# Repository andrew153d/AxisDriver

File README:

# Axis Driver #

# Json interface #

- To run the motor:
 ```
 {
  "type":"MOVEMENT",
  "mode": "POSITION",
  "steps": 1000,
  "speed": 100, 
  "stepmode": 64,
  "hold": 0
  }
```

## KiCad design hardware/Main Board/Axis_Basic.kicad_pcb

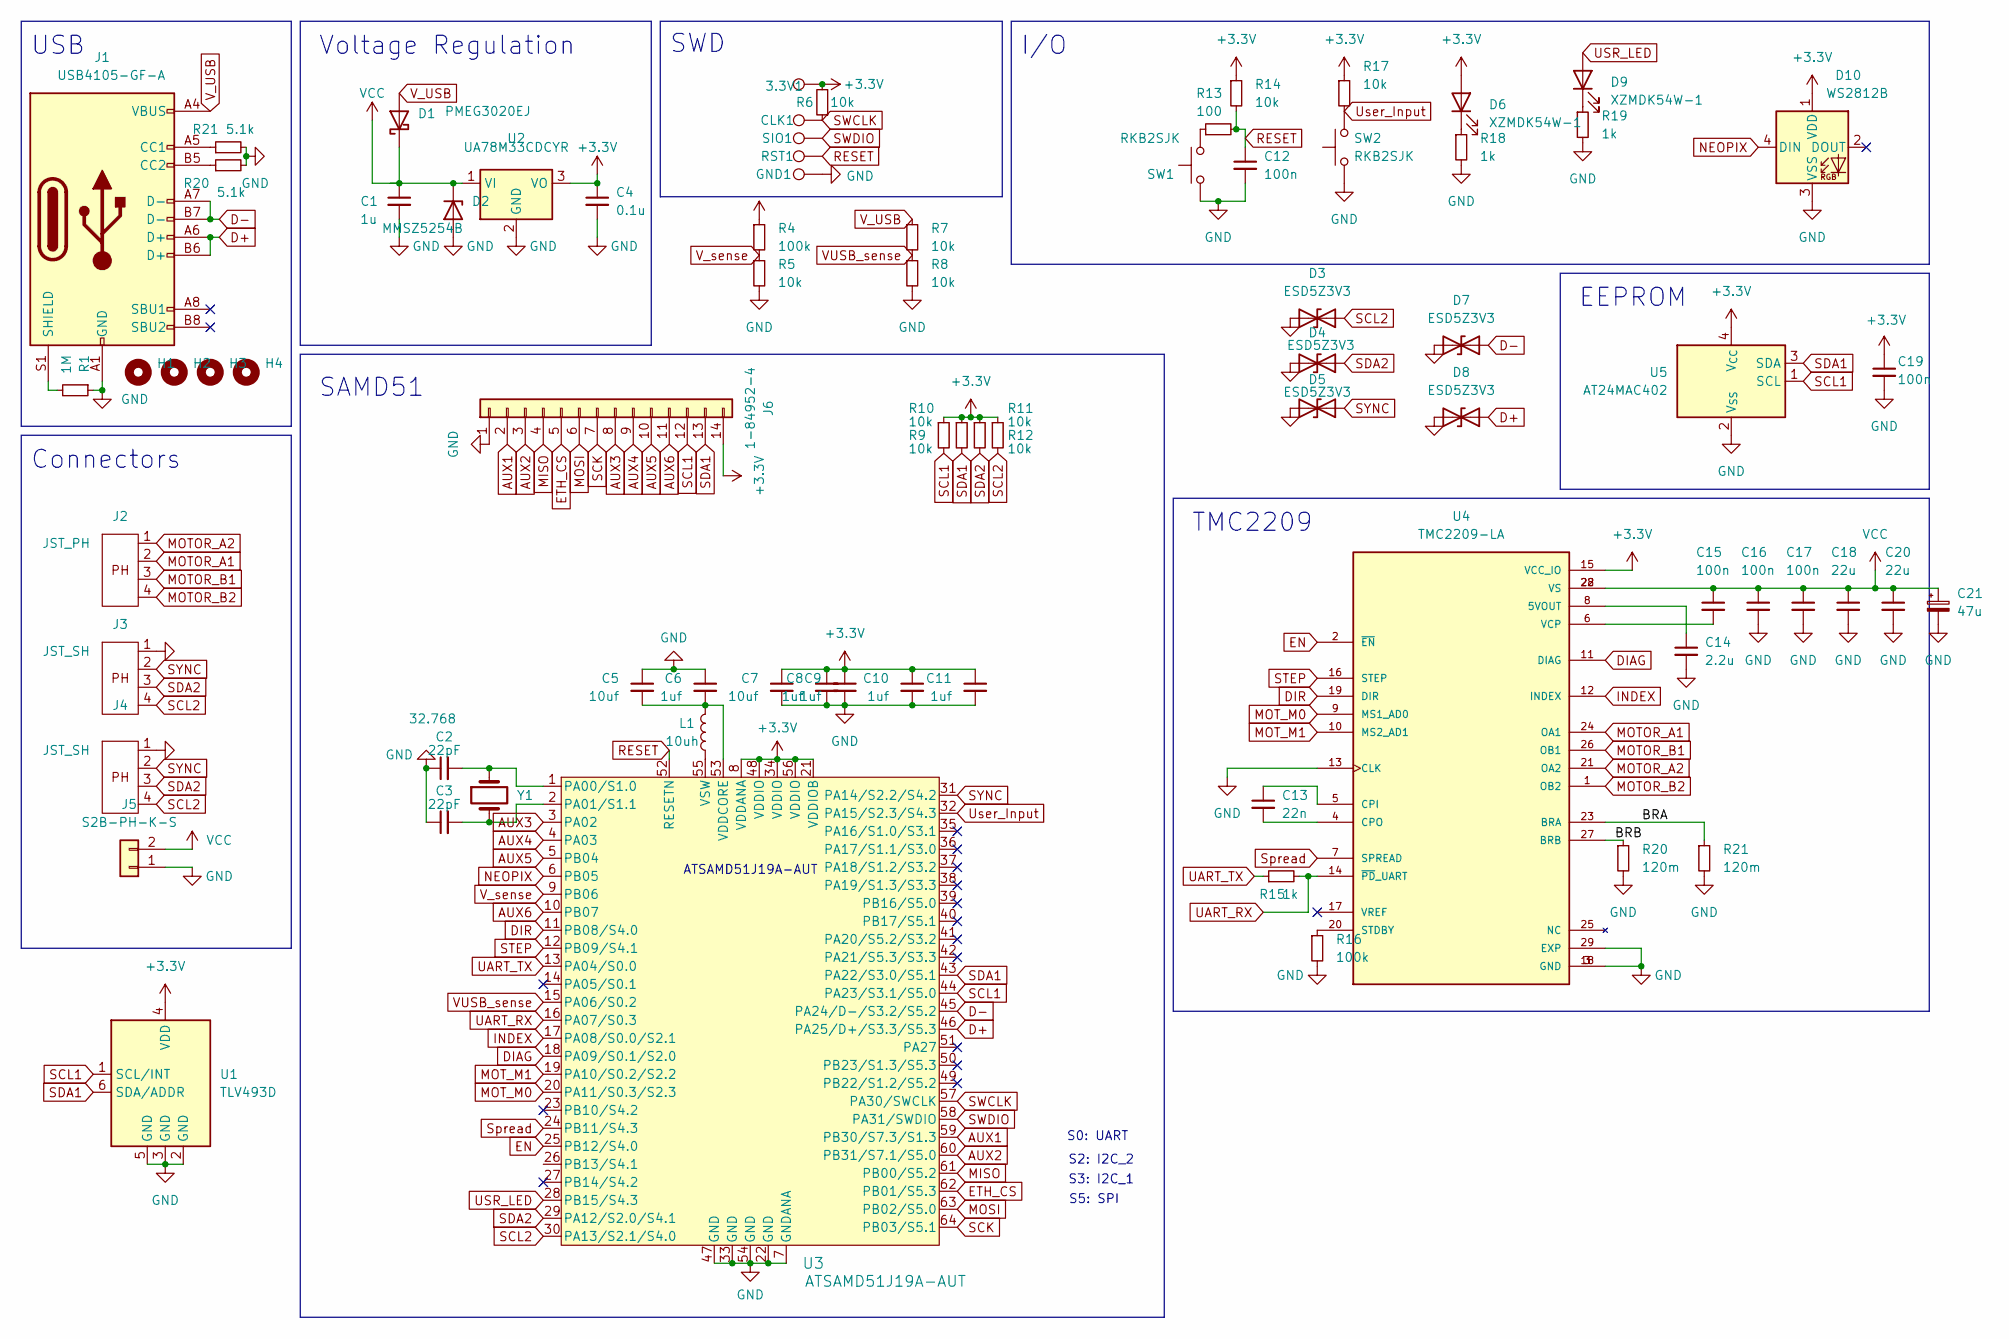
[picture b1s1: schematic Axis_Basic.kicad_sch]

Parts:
3.3V1: TestPoint; TestPoint_Pad_D2.0mm
C1: 1u; C_0402_1005Metric
C2, C3: 22pF; C_0402_1005Metric
C4: 0.1u; C_0402_1005Metric
C5, C7: 10uf; C_0805_2012Metric
C6, C8, C9, C10, C11: 1uf; C_0402_1005Metric
C12, C15, C16, C17, C19: 100n; C_0402_1005Metric
C13: 22n; C_0402_1005Metric
C14: 2.2u; C_0402_1005Metric
C18, C20: 22u; C_0805_2012Metric
C21: 47u; CP_Elec_6.3x5.4
CLK1: TestPoint; TestPoint_Pad_D2.0mm
D1: PMEG3020EJ; D_SOD-323F
D2: MMSZ5254B; D_SOD-123
D3, D4, D5, D7, D8: ESD5Z3V3; D_SOD-523
D6, D9: XZMDK54W-1; LED_0603_1608Metric
D10: WS2812B; LED_WS2812B_PLCC4_5.0x5.0mm_P3.2mm
GND1: TestPoint; TestPoint_Pad_D2.0mm
H1, H2, H3, H4: MountingHole; MountingHole_3.2mm_M3_ISO14580_Pad
J1: USB4105-GF-A; USB_C_Receptacle_GCT_USB4105-xx-A_16P_TopMnt_Horizontal
J2: JST_PH; JST_PH_S4B-PH-K_1x04_P2.00mm_Horizontal
J3, J4: JST_SH; JST_SH_SM04B-SRSS-TB_1x04-1MP_P1.00mm_Horizontal
J5: S2B-PH-K-S; JST_PH_S2B-PH-K_1x02_P2.00mm_Horizontal
J6: 1-84952-4; TE_1-84952-4_1x14-1MP_P1.0mm_Horizontal
L1: 10uh; L_0603_1608Metric
R1: 1M; R_0402_1005Metric
R4, R16: 100k; R_0402_1005Metric
R5, R6, R7, R8, R9, R10, R11, R12, R14, R17: 10k; R_0402_1005Metric
R13: 100; R_0402_1005Metric
R15, R18, R19: 1k; R_0402_1005Metric
R20, R21: 5.1k; R_0402_1005Metric
RST1: TestPoint; TestPoint_Pad_D2.0mm
SIO1: TestPoint; TestPoint_Pad_D2.0mm
SW1, SW2: RKB2SJK; button_RKB2SJK250SMTR LFS
U1: TLV493D; SOT-23-6
U2: UA78M33CDCYR; SOT-223-3_TabPin2
U3: ATSAMD51J19A-AUT; TQFP-64_10x10mm_P0.5mm
U4: TMC2209-LA; QFN-28-1EP_5x5mm_P0.5mm_EP3.35x3.35mm_ThermalVias; PARTREV 1.08
U5: AT24MAC402; SOT-23-5
Y1: 32.768; Crystal_SMD_3215-2Pin_3.2x1.5mm

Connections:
+3.3V: 3.3V1.1, C4.1, C7.1, C8.1, C9.1, C10.1, C11.1, C19.1, D6.2 (A), D10.1 (VDD), J6.14, R6.2, R9.1, R10.1, R11.1, R12.1, R14.1, R17.1, U1.4 (VDD), U2.3 (VO), U3.8 (VDDANA), U3.21 (VDDIOB), U3.34 (VDDIO), U3.48 (VDDIO), U3.56 (VDDIO), U4.15 (VCC_IO), U5.4 (V_{CC})
AUX1: J6.2, U3.59 (PB30/S7.3/S1.3)
AUX2: J6.3, U3.60 (PB31/S7.1/S5.0)
AUX3: J6.8, U3.3 (PA02)
AUX4: J6.9, U3.4 (PA03)
AUX5: J6.10, U3.5 (PB04)
AUX6: J6.11, U3.10 (PB07)
D+: D8.1 (A1), J1.A6 (D+), J1.B6 (D+), U3.46 (PA25/D+/S3.3/S5.3)
D-: D7.1 (A1), J1.A7 (D-), J1.B7 (D-), U3.45 (PA24/D-/S3.2/S5.2)
DIAG: U3.18 (PA09/S0.1/S2.0), U4.11 (DIAG)
DIR: U3.11 (PB08/S4.0), U4.19 (DIR)
EN: U3.25 (PB12/S4.0), U4.2 (~EN)
ETH_CS: J6.5, U3.62 (PB01/S5.3)
GND: C1.2, C2.1, C3.1, C4.2, C5.1, C6.1, C7.2, C8.2, C9.2, C10.2, C11.2, C12.2, C14.2, C16.2, C17.2, C18.2, C19.2, C20.2, C21.2, D2.2 (A), D3.2 (A2), D4.2 (A2), D5.2 (A2), D7.2 (A2), D8.2 (A2), D10.3 (VSS), GND1.1, J1.A1 (GND), J1.A12 (GND), J1.B1 (GND), J1.B12 (GND), J3.1, J4.1, J5.1, J6.1, R1.1, R5.2, R8.2, R16.2, R18.2, R19.2, R20.2, R21.2, SW1.1, SW2.1, U1.2 (GND), U1.3 (GND), U1.5 (GND), U2.2 (GND), U3.7 (GNDANA), U3.22 (GND), U3.33 (GND), U3.47 (GND), U3.54 (GND), U4.3 (GND), U4.13 (CLK), U4.18 (GND), U4.29 (EXP), U5.2 (V_{SS}); also elsewhere on the board
INDEX: U3.17 (PA08/S0.0/S2.1), U4.12 (INDEX)
MISO: J6.4, U3.61 (PB00/S5.2)
MOSI: J6.6, U3.63 (PB02/S5.0)
MOTOR_A1: J2.2, U4.24 (OA1)
MOTOR_A2: J2.1, U4.21 (OA2)
MOTOR_B1: J2.3, U4.26 (OB1)
MOTOR_B2: J2.4, U4.1 (OB2)
MOT_M0: U3.20 (PA11/S0.3/S2.3), U4.9 (MS1_AD0)
MOT_M1: U3.19 (PA10/S0.2/S2.2), U4.10 (MS2_AD1)
NEOPIX: D10.4 (DIN), U3.6 (PB05)
unnamed: D6.1 (K), R18.1
unnamed: D9.1 (K), R19.1
unnamed: J1.S1 (SHIELD), R1.2
unnamed: R13.1, SW1.2
unnamed: C2.2, U3.1 (PA00/S1.0), Y1.1
unnamed: C3.2, U3.2 (PA01/S1.1), Y1.2
unnamed: C5.2, C6.2, L1.2, U3.53 (VDDCORE)
unnamed: L1.1, U3.55 (VSW)
unnamed: C14.1, U4.8 (5VOUT)
unnamed: C13.1, U4.5 (CPI)
unnamed: C13.2, U4.4 (CPO)
unnamed: R16.1, U4.20 (STDBY)
unnamed: C15.2, U4.6 (VCP)
RESET: C12.1, R13.2, R14.2, RST1.1, U3.52 (RESETN)
SCK: J6.7, U3.64 (PB03/S5.1)
SCL1: J6.12, R9.2, U1.1 (SCL/INT), U3.44 (PA23/S3.1/S5.0), U5.1 (SCL)
SCL2: D3.1 (A1), J3.4, J4.4, R12.2, U3.30 (PA13/S2.1/S4.0)
SDA1: J6.13, R10.2, U1.6 (SDA/ADDR), U3.43 (PA22/S3.0/S5.1), U5.3 (SDA)
SDA2: D4.1 (A1), J3.3, J4.3, R11.2, U3.29 (PA12/S2.0/S4.1)
STEP: U3.12 (PB09/S4.1), U4.16 (STEP)
SWCLK: CLK1.1, R6.1, U3.57 (PA30/SWCLK)
SWDIO: SIO1.1, U3.58 (PA31/SWDIO)
SYNC: D5.1 (A1), J3.2, J4.2, U3.31 (PA14/S2.2/S4.2)
Spread: U3.24 (PB11/S4.3), U4.7 (SPREAD)
UART_RX: R15.2, U3.16 (PA07/S0.3), U4.14 (~PD_UART)
UART_TX: R15.1, U3.13 (PA04/S0.0)
USR_LED: D9.2 (A), U3.28 (PB15/S4.3)
User_Input: R17.2, SW2.2, U3.32 (PA15/S2.3/S4.3)
VCC: C1.1, C15.1, C16.1, C17.1, C18.1, C20.1, C21.1, D1.1 (K), D2.1 (K), J5.2, R4.1, U2.1 (VI), U4.22 (VS), U4.28 (VS)
VUSB_sense: R7.2, R8.1, U3.15 (PA06/S0.2)
V_USB: D1.2 (A), J1.A4 (VBUS), J1.A9 (VBUS), J1.B4 (VBUS), J1.B9 (VBUS), R7.1
V_sense: R4.2, R5.1, U3.9 (PB06)

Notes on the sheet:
S2: I2C_2
SAMD51
EEPROM
S3: I2C_1
Connectors
TMC2209
I/O
ATSAMD51J19A-AUT
Voltage Regulation
S0: UART
SWD
S5: SPI
USB

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
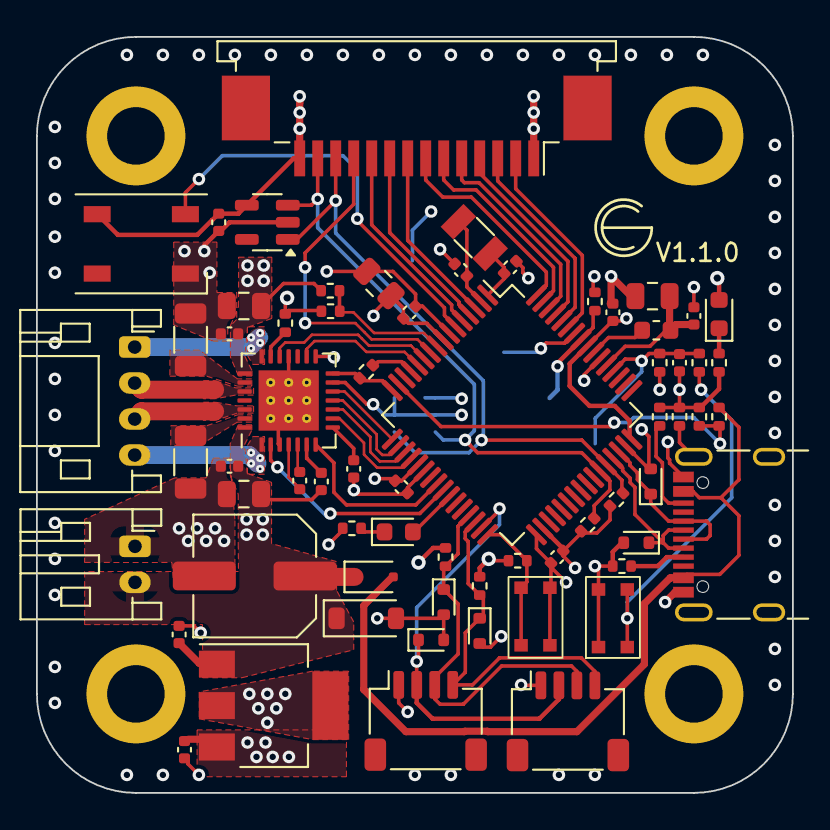
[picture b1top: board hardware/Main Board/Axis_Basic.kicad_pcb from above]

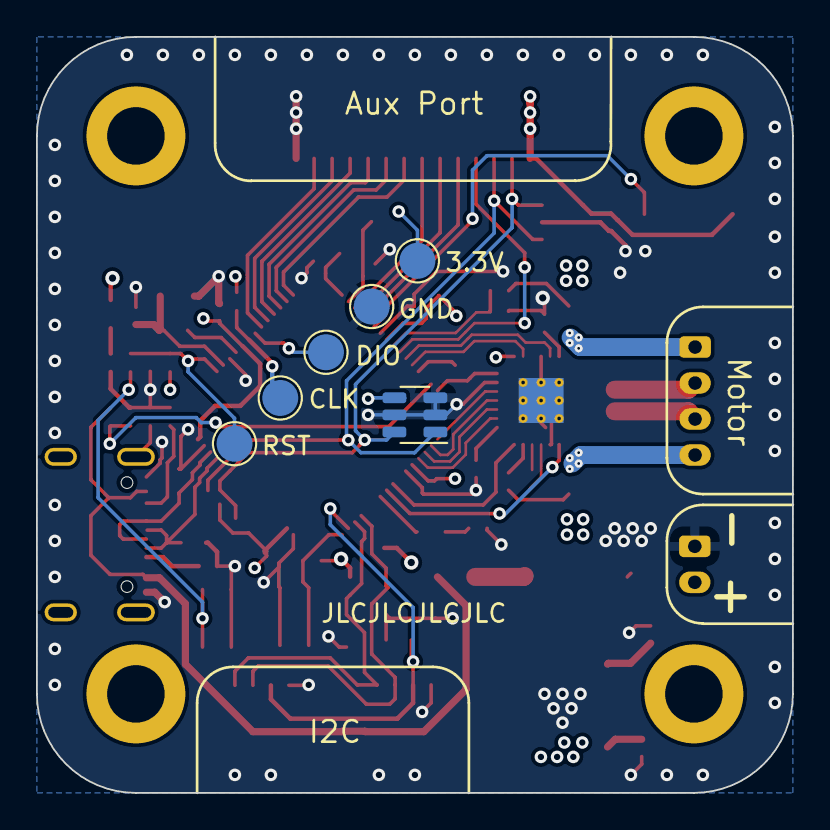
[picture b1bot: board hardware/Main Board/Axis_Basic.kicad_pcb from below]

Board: 4 copper layers, 42.0 x 42.0 mm, 76 parts (6 on the bottom side), 60 nets.

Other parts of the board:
R2, R3: 5.1k; R_0402_1005Metric

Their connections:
GND: R2.2, R3.2; also elsewhere on the board

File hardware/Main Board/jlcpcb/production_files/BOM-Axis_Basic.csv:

Comment,Designator,Footprint,LCSC
100n,"C12,C15",C_0402_1005Metric,C1525
10k,"R11,R12,R6,R9",R_0402_1005Metric,C25744
5.1k,"R2,R3",R_0402_1005Metric,C25905
1M,R1,R_0402_1005Metric,C26083
TMC2209-LA,U4,QFN-28-1EP_5x5mm_P0.5mm_EP3.35x3.35mm_ThermalVias,C465949
UA78M33CDCYR,U2,SOT-223-3_TabPin2,C49036
1uf,C6,C_0402_1005Metric,
22pF,C3,C_0402_1005Metric,
10k,R10,R_0402_1005Metric,
0.33u,C1,C_0402_1005Metric,
ESD5Z3V3,D4,D_SOD-523,
ATSAMD51J19A-AUT,U3,TQFP-64_10x10mm_P0.5mm,
JST_SH,J4,JST_SH_SM04B-SRSS-TB_1x04-1MP_P1.00mm_Horizontal,
ESD5Z3V3,D5,D_SOD-523,
10uf,C5,C_0805_2012Metric,
1-84952-4,J6,TE_1-84952-4_1x14-1MP_P1.0mm_Horizontal,
MountingHole,H1,MountingHole_3.2mm_M3_ISO14580_Pad,
1k,R15,R_0402_1005Metric,
100k,R4,R_0402_1005Metric,
1uf,C9,C_0402_1005Metric,
0.1u,C4,C_0402_1005Metric,
10k,R5,R_0402_1005Metric,
1uf,C8,C_0402_1005Metric,
JST_PH,J2,JST_PH_S4B-PH-K_1x04_P2.00mm_Horizontal,
ESD5Z3V3,D3,D_SOD-523,
32.768,Y1,Crystal_SMD_3215-2Pin_3.2x1.5mm,
10k,R8,R_0402_1005Metric,
MountingHole,H4,MountingHole_3.2mm_M3_ISO14580_Pad,
1uf,C11,C_0402_1005Metric,
100n,C17,C_0402_1005Metric,
XZMDK54W-1,D6,LED_0603_1608Metric,
100n,C16,C_0402_1005Metric,
ESD5Z3V3,D7,D_SOD-523,
1uf,C10,C_0402_1005Metric,
PMEG3020EJ,D1,D_SOD-323F,
RKB2SJK,SW1,button_RKB2SJK250SMTR LFS,
24AA02E-OT,U5,SOT-23-5,
22u,C18,C_0805_2012Metric,
2.2u,C14,C_0402_1005Metric,
RKB2SJK,SW2,button_RKB2SJK250SMTR LFS,
	MMSZ5254B,D2,D_SOD-123,
22pF,C2,C_0402_1005Metric,
10uf,C7,C_0805_2012Metric,
10k,R7,R_0402_1005Metric,
MountingHole,H3,MountingHole_3.2mm_M3_ISO14580_Pad,
22n,C13,C_0402_1005Metric,
300,R13,R_0402_1005Metric,
10k,R14,R_0402_1005Metric,
JST_SH,J3,JST_SH_SM04B-SRSS-TB_1x04-1MP_P1.00mm_Horizontal,
S2B-PH-K-S,J5,JST_PH_S2B-PH-K_1x02_P2.00mm_Horizontal,
MountingHole,H2,MountingHole_3.2mm_M3_ISO14580_Pad,
USB4105-GF-A,J1,USB_C_Receptacle_GCT_USB4105-xx-A_16P_TopMnt_Horizontal,
TLV493D,U1,SOT-23-6,
120m,R21,R_1206_3216Metric,
100k,R16,R_0402_1005Metric,
1k,R19,R_0402_1005Metric,
10uh,L1,L_0603_1608Metric,
47u,C21,CP_Elec_6.3x5.4,
XZMDK54W-1,D9,LED_0603_1608Metric,
22u,C20,C_0805_2012Metric,
100n,C19,C_0402_1005Metric,
1k,R18,R_0402_1005Metric,
10k,R17,R_0402_1005Metric,
WS2812B,D10,LED_WS2812B_PLCC4_5.0x5.0mm_P3.2mm,
120m,R20,R_1206_3216Metric,
ESD5Z3V3,D8,D_SOD-523,
TestPoint,GND1,TestPoint_Pad_D2.0mm,
TestPoint,CLK1,TestPoint_Pad_D2.0mm,
TestPoint,RST1,TestPoint_Pad_D2.0mm,
TestPoint,SIO1,TestPoint_Pad_D2.0mm,

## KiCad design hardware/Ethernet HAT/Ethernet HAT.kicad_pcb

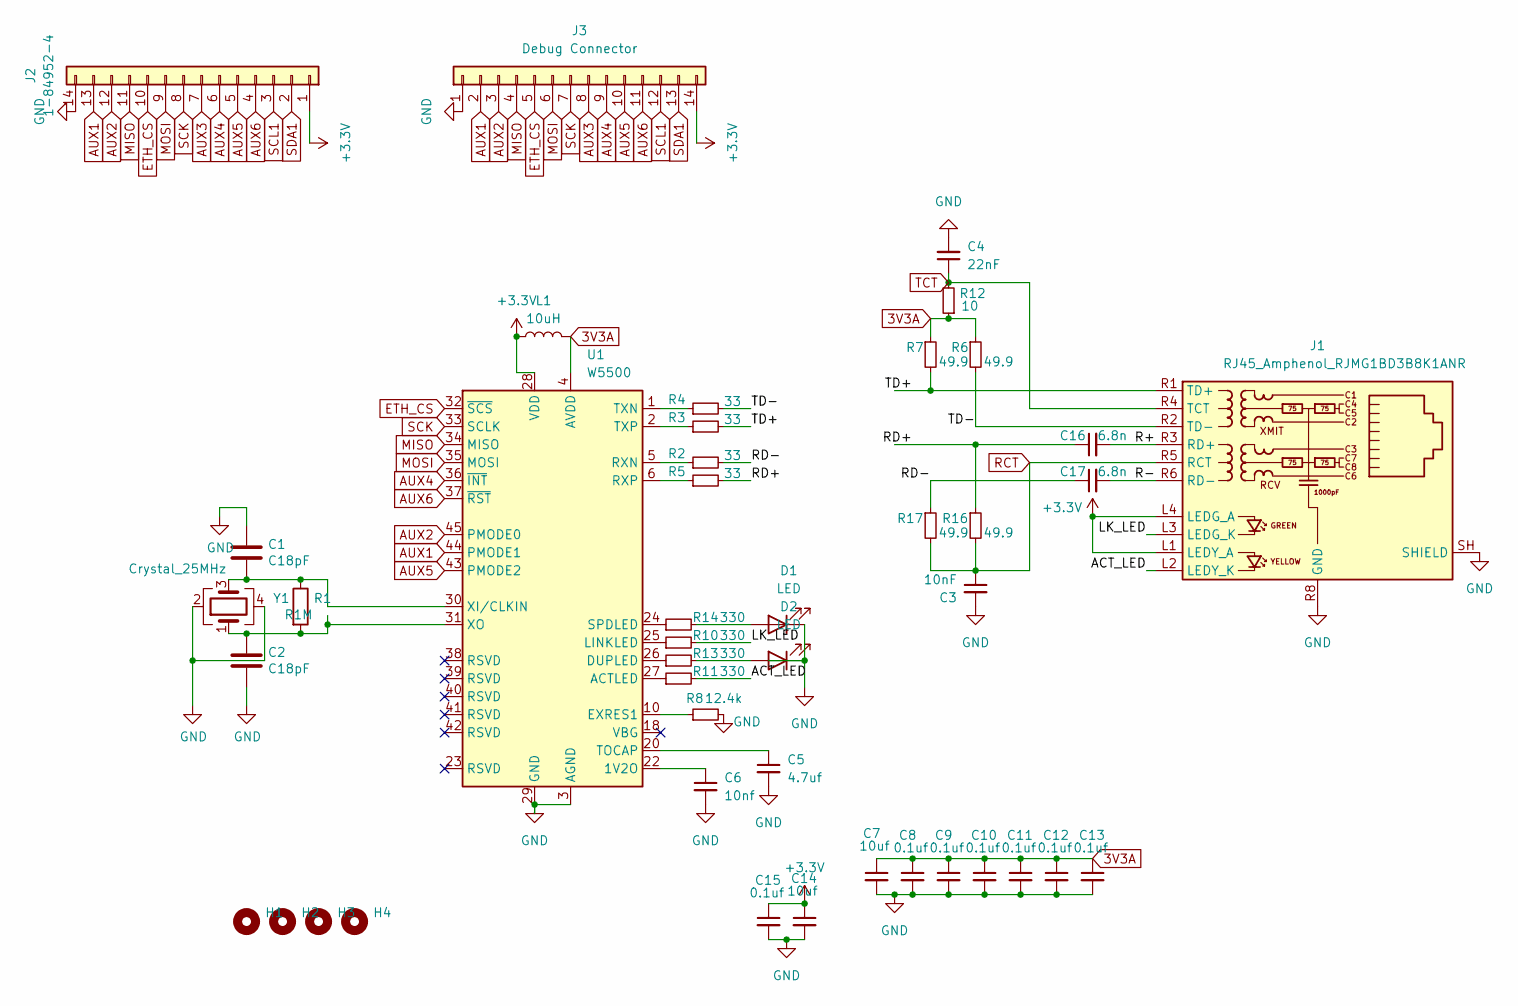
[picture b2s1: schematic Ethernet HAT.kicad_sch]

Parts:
C1, C2: C18pF; C_0402_1005Metric; LCSC C1549
C3: 10nF; C_0402_1005Metric
C4: 22nF; C_0402_1005Metric
C5: 4.7uf; C_0402_1005Metric
C6: 10nf; C_0402_1005Metric
C7, C14: 10uf; C_0805_2012Metric
C8, C9, C10, C11, C12, C13, C15: 0.1uf; C_0402_1005Metric
C16, C17: 6.8n; C_0402_1005Metric
D1, D2: LED; LED_0603_1608Metric
H1, H2, H3, H4: MountingHole; MountingHole_3.2mm_M3_ISO14580_Pad
J1: RJ45_Amphenol_RJMG1BD3B8K1ANR
J2: 1-84952-4; TE_1-84952-4_1x14-1MP_P1.0mm_Horizontal
J3: Debug Connector; Conn_01x14_Flat2.54
L1: 10uH; L_0603_1608Metric
R1: R1M; R_0402_1005Metric; LCSC C26083
R2, R3, R4, R5: 33; R_0402_1005Metric
R6, R7, R16, R17: 49.9; R_0402_1005Metric
R8: 12.4k; R_0603_1608Metric
R10, R11, R13, R14: 330; R_0402_1005Metric
R12: 10; R_0402_1005Metric
U1: W5500; LQFP-48_7x7mm_P0.5mm
Y1: Crystal_25MHz; Crystal_SMD_3225-4Pin_3.2x2.5mm; LCSC C9006

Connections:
3V3A: C7.1, C8.1, C9.1, C10.1, C11.1, C12.1, C13.1, L1.2, R6.1, R7.1, R12.1, U1.4 (AVDD), U1.8 (AVDD), U1.11 (AVDD), U1.15 (AVDD), U1.17 (AVDD), U1.21 (AVDD)
+3.3V: C14.1, C15.1, J1.L1 (LEDY_A), J1.L4 (LEDG_A), J2.1, J3.14, L1.1, U1.28 (VDD)
/ACT_LED: J1.L2 (LEDY_K), R11.2
/LK_LED: J1.L3 (LEDG_K), R10.2
/R+: C16.2, J1.R3 (RD+)
/R-: C17.2, J1.R6 (RD-)
/RD+: C16.1, R5.2, R16.1
/RD-: C17.1, R2.2, R17.1
/TD+: J1.R1 (TD+), R3.2, R7.2
/TD-: J1.R2 (TD-), R4.2, R6.2
AUX1: J2.13, J3.2, U1.44 (PMODE1)
AUX2: J2.12, J3.3, U1.45 (PMODE0)
AUX3: J2.7, J3.8
AUX4: J2.6, J3.9, U1.36 (~INT)
AUX5: J2.5, J3.10, U1.43 (PMODE2)
AUX6: J2.4, J3.11, U1.37 (~RST)
ETH_CS: J2.10, J3.5, U1.32 (~SCS)
GND: C1.1, C2.2, C3.2, C4.2, C5.2, C6.2, C7.2, C8.2, C9.2, C10.2, C11.2, C12.2, C13.2, C14.2, C15.2, D1.1 (K), D2.1 (K), J1.R8 (GND), J1.SH (SHIELD), J2.14, J3.1, R8.2, U1.3 (AGND), U1.9 (AGND), U1.14 (AGND), U1.16 (AGND), U1.19 (AGND), U1.29 (GND), U1.48 (AGND), Y1.2, Y1.4
MISO: J2.11, J3.4, U1.34 (MISO)
MOSI: J2.9, J3.6, U1.35 (MOSI)
unnamed: D1.2 (A), R14.2
unnamed: D2.2 (A), R13.2
unnamed: C6.1, U1.22 (1V2O)
unnamed: R11.1, U1.27 (ACTLED)
unnamed: R13.1, U1.26 (DUPLED)
unnamed: R8.1, U1.10 (EXRES1)
unnamed: R10.1, U1.25 (LINKLED)
unnamed: R2.1, U1.5 (RXN)
unnamed: R5.1, U1.6 (RXP)
unnamed: R14.1, U1.24 (SPDLED)
unnamed: C5.1, U1.20 (TOCAP)
unnamed: R4.1, U1.1 (TXN)
unnamed: R3.1, U1.2 (TXP)
unnamed: C1.2, R1.1, U1.30 (XI/CLKIN), Y1.3
unnamed: C2.1, R1.2, U1.31 (XO), Y1.1
RCT: C3.1, J1.R5 (RCT), R16.2, R17.2
SCK: J2.8, J3.7, U1.33 (SCLK)
SCL1: J2.3, J3.12
SDA1: J2.2, J3.13
TCT: C4.1, J1.R4 (TCT), R12.2

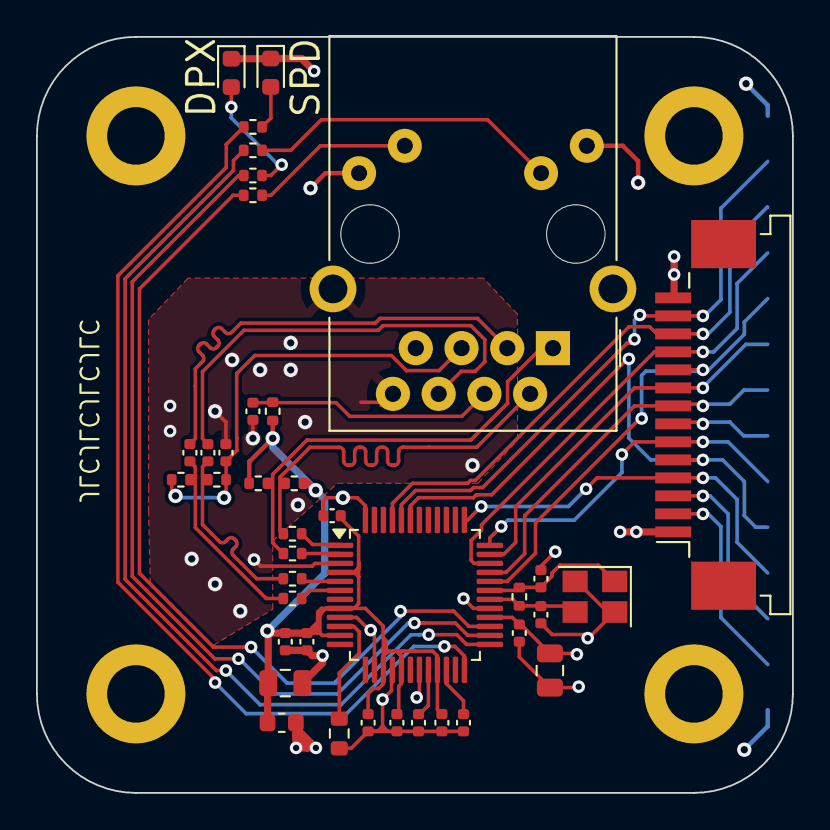
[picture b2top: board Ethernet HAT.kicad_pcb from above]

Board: 4 copper layers, 42.0 x 42.0 mm, 44 parts (1 on the bottom side), 40 nets.

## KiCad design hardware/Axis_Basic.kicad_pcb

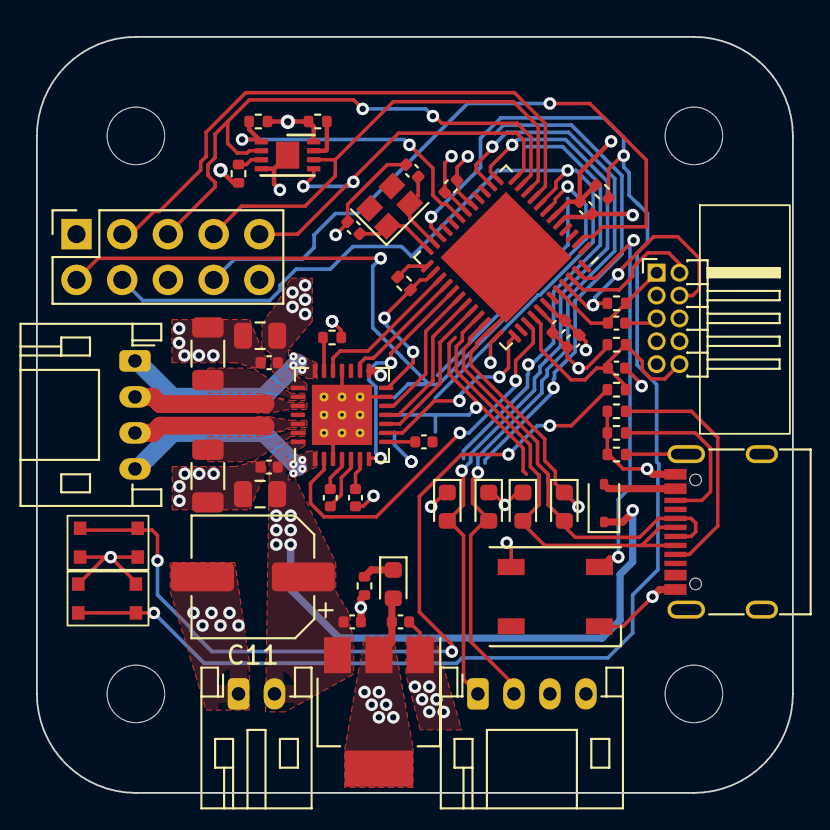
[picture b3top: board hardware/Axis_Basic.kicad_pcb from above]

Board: 4 copper layers, 42.0 x 42.0 mm, 58 parts (1 on the bottom side), 51 nets.

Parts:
C1: 0.47u Tant.; C_0402_1005Metric
C2: 22u Tant.; C_0402_1005Metric
C3, C6, C7, C8, C12, C13, C14, C15: 100n; C_0402_1005Metric
C4: 22n; C_0402_1005Metric
C5: 2.2u; C_0402_1005Metric
C9, C10: 22u; C_0805_2012Metric
C11: 47u; CP_Elec_6.3x5.4
C16: 4.7u; C_0402_1005Metric
C17, C18: 1pF; C_0402_1005Metric
D1: NSR0530HT1G; D_SOD-323
D2, D3, D4, D6: GSEN3U003; D_0603_1608Metric
D5: XZMDK54W-1; LED_0603_1608Metric
D7: WS2812B; LED_WS2812B_PLCC4_5.0x5.0mm_P3.2mm
H1, H2, H3, H4: MountingHole; MountingHole_3.2mm_M3
J1: USB_C_Receptacle_USB2.0; USB_C_Receptacle_G-Switch_GT-USB-7010ASV
J2, J3: JST_PH; JST_PH_S4B-PH-K_1x04_P2.00mm_Horizontal
J4: S2B-PH-K-S; JST_PH_S2B-PH-K_1x02_P2.00mm_Horizontal
J5: 1175-1628-ND; PinHeader_2x05_P1.27mm_Horizontal
J6: Conn_01x10; PinSocket_2x05_P2.54mm_Vertical
R1: 1M; R_0402_1005Metric
R2, R3: 5.1k; R_0402_1005Metric
R4, R7, R10: 1k; R_0402_1005Metric
R5: 300; R_0402_1005Metric
R6, R9, R11, R12, R13: 10k; R_0402_1005Metric
R8: 100k; R_0402_1005Metric
R14, R15: 120m; R_1206_3216Metric
SW1, SW2: RKB2SJK; button_RKB2SJK250SMTR LFS
U1: TLV493D; SOT-23-6
U2: UA78M33CDCYR; SOT-223-3_TabPin2
U3: ATSAMD51G18A-MU; VQFN-48-1EP_7x7mm_P0.5mm_EP5.15x5.15mm
U4: TMC2209-LA; QFN-28-1EP_5x5mm_P0.5mm_EP3.35x3.35mm_ThermalVias
U5: AT25040B-MAHL-T; DFN-8-1EP_3x2mm_P0.5mm_EP1.3x1.5mm
Y1: SG-210STF 48.0000ML0; Crystal_SMD_2520-4Pin_2.5x2.0mm

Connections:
+3.3V: C2.1, C12.1, C13.1, C14.1, C15.1, C16.1, D5.2 (A), D7.1 (VDD), J5.1 (VTref), J6.10, R4.2, R6.1, R9.1, R11.1, R12.1, R13.1, U1.4 (VDD), U2.2 (VO), U3.6 (VDDANA), U3.17 (VDDIO), U3.36 (VDDIO), U3.41 (VDDCORE), U3.44 (VDDIO), U4.15 (VCC_IO), U5.8 (VCC)
/BRA: R15.1, U4.23 (BRA)
/BRB: R14.1, U4.27 (BRB)
D+: D4.2 (A2), J1.A6 (D+), J1.B6 (D+), U3.34 (PA25/SERCOM3_3/SERCOM5_3)
D-: D6.2 (A2), J1.A7 (D-), J1.B7 (D-), U3.33 (PA24/SERCOM3_2/SERCOM5_2)
DIAG: U3.31 (PA22/SERCOM3_0/SERCOM5_1), U4.11 (DIAG)
DIR: U3.27 (PA18/SERCOM1_2/SERCOM3_2), U4.19 (DIR)
EEPROM_CS: R13.2, U3.19 (PB10/SEROM4_2), U5.1 (~CS)
EN: U3.39 (PA27), U4.2 (~EN)
ETH_CS: J6.3, U3.9 (PA04/SERCOM0_0)
GND: C1.2, C2.2, C3.2, C5.2, C7.2, C8.2, C9.2, C10.2, C11.2, C12.2, C13.2, C14.2, C15.2, C16.2, C17.1, C18.1, D2.1 (A1), D3.1 (A1), D4.1 (A1), D6.1 (A1), D7.3 (VSS), J1.A1 (GND), J1.A12 (GND), J1.B1 (GND), J1.B12 (GND), J3.4, J4.1, J5.3 (GND), J5.5 (GND), J5.9 (GNDDetect), J6.1, R1.1, R2.2, R3.2, R8.2, R10.2, R14.2, R15.2, SW1.1, SW2.1, U1.2 (GND), U1.3 (GND), U1.5 (GND), U2.1 (GND), U3.5 (GNDANA), U3.18 (GND), U3.35 (GND), U3.42 (GND), U3.49 (PAD), U4.3 (GND), U4.13 (CLK), U4.18 (GND), U4.29 (EXP), U5.4 (GND), U5.9 (GND)
INDEX: U3.30 (PA21/SERCOM5_3/SERCOM3_3), U4.12 (INDEX)
MISO: J6.5, U3.11 (PA06/SERCOM0_2), U5.2 (MISO)
MOSI: J6.9, U3.12 (PA07/SERCOM0_3), U5.5 (MOSI)
MOTOR_A1: J2.1, U4.21 (OA2)
MOTOR_A2: J2.3, U4.26 (OB1)
MOTOR_B1: J2.2, U4.24 (OA1)
MOTOR_B2: J2.4, U4.1 (OB2)
MOT_M0: U3.37 (PB22/SERCOM1_2/SERCOM5_2), U4.9 (MS1_AD0)
MOT_M1: U3.32 (PA23/SERCOM3_1/SERCOM5_0), U4.10 (MS2_AD1)
NEOPIX: D7.4 (DIN), U3.47 (PB02/SERCOM5_0)
unnamed: D5.1 (K), R10.1
unnamed: J1.A5 (CC1), R2.1
unnamed: J1.B5 (CC2), R3.1
unnamed: J1.S1 (SHIELD), R1.2
unnamed: J6.8, U3.2 (PA01/SERCOM1_1)
unnamed: R5.1, SW1.2
unnamed: C17.2, U3.23 (PA14/SERCOM2_2/SERCOM4_2), Y1.2
unnamed: C18.2, U3.24 (PA15/SERCOM2_3/SERCOM4_3), Y1.1
unnamed: C5.1, U4.8 (5VOUT)
unnamed: C4.1, U4.5 (CPI)
unnamed: C4.2, U4.4 (CPO)
unnamed: R8.1, U4.20 (STDBY)
unnamed: C6.2, U4.6 (VCP)
unnamed: R12.2, U5.7 (~HOLD)
unnamed: R11.2, U5.3 (~WP)
RESET: C3.1, J5.10 (~RESET), R5.2, R6.2, U3.40 (nRESET)
SCK: J6.7, U3.10 (PA05/SERCOM0_1), U5.6 (SCK)
SCL1: J6.4, U1.1 (SCL/INT), U3.8 (PB09/SERCOM4_1)
SCL2: D2.2 (A2), J3.1, U3.13 (PA08/SERCOM0_0/SERCOM2_1)
SDA1: J6.2, U1.6 (SDA/ADDR), U3.7 (PB08/SERCOM4_0)
SDA2: D3.2 (A2), J3.2, U3.14 (PA09/SEROM0_1/SERCOM2_0)
STEP: U3.28 (PA19/SERCOM1_3/SERCOM3_3), U4.16 (STEP)
SWCLK: J5.4 (SWDCLK/TCK), R4.1, U3.45 (PA30/SWCLK)
SWDIO: J5.2 (SWDIO/TMS), U3.46 (PA31/SWDIO)
Spread: U3.29 (PA20/SERCOM5_2/SERCOM3_2), U4.7 (SPREAD)
UART_RX: R7.2, U3.26 (PA14/SERCOM1_1/SERCOM3_0), U4.14 (~PD_UART)
UART_TX: R7.1, U3.25 (PA16/SERCOM1_0/SERCOM3_1)
User_Input: R9.2, SW2.2, U3.22 (PA13/SERCOM2_1/SERCOM4_0)
VCC: C1.1, C6.1, C7.1, C8.1, C9.1, C10.1, C11.1, D1.1 (K), J4.2, U2.3 (VI), U4.22 (VS), U4.28 (VS)
V_USB: D1.2 (A), J1.A4 (VBUS), J1.A9 (VBUS), J1.B4 (VBUS), J1.B9 (VBUS)

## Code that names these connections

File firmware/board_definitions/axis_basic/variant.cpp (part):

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
const PinDescription g_APinDescription[]=
{
// SYNC (0) PA14
  { PORTA, 14, PIO_DIGITAL, PIN_ATTR_DIGITAL, No_ADC_Channel, NOT_ON_PWM, NOT_ON_TIMER, EXTERNAL_INT_NONE },

//Auxiliary Ports
// PA02 (1)
  { PORTA,  2, PIO_DIGITAL, PIN_ATTR_DIGITAL, No_ADC_Channel, NOT_ON_PWM, NOT_ON_TIMER, EXTERNAL_INT_NONE },
// PA03 (2)
  { PORTA,  3, PIO_DIGITAL, PIN_ATTR_DIGITAL, No_ADC_Channel, NOT_ON_PWM, NOT_ON_TIMER, EXTERNAL_INT_NONE },
// PB04 (3)
  { PORTB,  4, PIO_DIGITAL, PIN_ATTR_DIGITAL, No_ADC_Channel, NOT_ON_PWM, NOT_ON_TIMER, EXTERNAL_INT_NONE },
// PB05 (4)
  { PORTA,  5, PIO_DIGITAL, PIN_ATTR_DIGITAL, No_ADC_Channel, NOT_ON_PWM, NOT_ON_TIMER, EXTERNAL_INT_NONE },
// PB30 (5)
  { PORTB,  30, PIO_DIGITAL, PIN_ATTR_DIGITAL, No_ADC_Channel, NOT_ON_PWM, NOT_ON_TIMER, EXTERNAL_INT_NONE },
// PB31 (6)
  { PORTB,  31, PIO_DIGITAL, PIN_ATTR_DIGITAL, No_ADC_Channel, NOT_ON_PWM, NOT_ON_TIMER, EXTERNAL_INT_NONE },
// //LEDS
// NEOPIX (7) PB05
  { PORTB, 5, PIO_DIGITAL, PIN_ATTR_NONE, No_ADC_Channel, NOT_ON_PWM, NOT_ON_TIMER, EXTERNAL_INT_NONE }, //neopix
// STAT_LED (8)
  { PORTB,  13, PIO_DIGITAL, PIN_ATTR_DIGITAL, No_ADC_Channel, NOT_ON_PWM, NOT_ON_TIMER, EXTERNAL_INT_NONE },
// //Motor Control
// EN (11) PB12
  { PORTB, 12, PIO_DIGITAL, PIN_ATTR_DIGITAL, No_ADC_Channel, NOT_ON_PWM, NOT_ON_TIMER, EXTERNAL_INT_NONE },
// DIR (12) PB08
  { PORTB,  8, PIO_DIGITAL, PIN_ATTR_DIGITAL, No_ADC_Channel, NOT_ON_PWM, NOT_ON_TIMER, EXTERNAL_INT_NONE },
// STEP (13) PB09
  { PORTB,  9, PIO_DIGITAL, PIN_ATTR_DIGITAL, No_ADC_Channel, NOT_ON_PWM, NOT_ON_TIMER, EXTERNAL_INT_NONE },
// MOT_M1 (14) PA10
  { PORTA,  10, PIO_DIGITAL, PIN_ATTR_DIGITAL, No_ADC_Channel, NOT_ON_PWM, NOT_ON_TIMER, EXTERNAL_INT_NONE },
// MOT_M0 (15) PA11
  { PORTA,  11, PIO_DIGITAL, PIN_ATTR_DIGITAL, No_ADC_Channel, NOT_ON_PWM, NOT_ON_TIMER, EXTERNAL_INT_NONE },
// INDEX (16) PA08
  { PORTA,  8, PIO_DIGITAL, PIN_ATTR_DIGITAL, No_ADC_Channel, NOT_ON_PWM, NOT_ON_TIMER, EXTERNAL_INT_NONE },
// DIAG (17) PA09
  { PORTB,  9, PIO_DIGITAL, PIN_ATTR_DIGITAL, No_ADC_Channel, NOT_ON_PWM, NOT_ON_TIMER, EXTERNAL_INT_NONE },
// SPREAD (18) PB11
  { PORTB,  11, PIO_DIGITAL, PIN_ATTR_DIGITAL, No_ADC_Channel, NOT_ON_PWM, NOT_ON_TIMER, EXTERNAL_INT_NONE },
// UART_RX (19) PA06
  { PORTA,  6, PIO_DIGITAL, PIN_ATTR_DIGITAL, No_ADC_Channel, NOT_ON_PWM, NOT_ON_TIMER, EXTERNAL_INT_NONE },
// UART_TX (20) PA07
  { PORTA,  7, PIO_DIGITAL, PIN_ATTR_DIGITAL, No_ADC_Channel, NOT_ON_PWM, NOT_ON_TIMER, EXTERNAL_INT_NONE },

// //Connectivity
// SDA2 (21) PA12
  { PORTA,  12, PIO_DIGITAL, PIN_ATTR_DIGITAL, No_ADC_Channel, NOT_ON_PWM, NOT_ON_TIMER, EXTERNAL_INT_NONE },
// SCL2 (22) PA13
  { PORTA,  13, PIO_DIGITAL, PIN_ATTR_DIGITAL, No_ADC_Channel, NOT_ON_PWM, NOT_ON_TIMER, EXTERNAL_INT_NONE },
// SDA1 (23) PB16
  { PORTB,  16, PIO_DIGITAL, PIN_ATTR_DIGITAL, No_ADC_Channel, NOT_ON_PWM, NOT_ON_TIMER, EXTERNAL_INT_NONE },
// SCL1 (24) PB17
  { PORTB,  17, PIO_DIGITAL, PIN_ATTR_DIGITAL, No_ADC_Channel, NOT_ON_PWM, NOT_ON_TIMER, EXTERNAL_INT_NONE },

// EEPROM_CS (25) PA21
  { PORTA,  21, PIO_DIGITAL, PIN_ATTR_DIGITAL, No_ADC_Channel, NOT_ON_PWM, NOT_ON_TIMER, EXTERNAL_INT_NONE },
// ETH_CS (26) PB03
  { PORTB,  3, PIO_DIGITAL, PIN_ATTR_DIGITAL, No_ADC_Channel, NOT_ON_PWM, NOT_ON_TIMER, EXTERNAL_INT_NONE },
// MOSI (27) PB00
  { PORTB,  0, PIO_DIGITAL, PIN_ATTR_DIGITAL, No_ADC_Channel, NOT_ON_PWM, NOT_ON_TIMER, EXTERNAL_INT_NONE  },
// MISO (28) PB01
  { PORTB,  1, PIO_DIGITAL, PIN_ATTR_DIGITAL, No_ADC_Channel, NOT_ON_PWM, NOT_ON_TIMER, EXTERNAL_INT_NONE },
// SCK (29) PB02
  { PORTB,  2, PIO_DIGITAL, PIN_ATTR_DIGITAL, No_ADC_Channel, NOT_ON_PWM, NOT_ON_TIMER, EXTERNAL_INT_NONE }


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  // { NOT_A_PORT, 0, PIO_NOT_A_PIN, PIN_ATTR_TIMER, No_ADC_Channel, NOT_ON_PWM, NOT_ON_TIMER, EXTERNAL_INT_NONE },

  // // Digital High
  // { PORTB, 3, PIO_DIGITAL, PIN_ATTR_DIGITAL, No_ADC_Channel, NOT_ON_PWM, NOT_ON_TIMER, EXTERNAL_INT_NONE }, //neopix
  // { PORTA,  19, PIO_TIMER_ALT, PIN_ATTR_PWM_F, No_ADC_Channel, TCC1_CH3, TC3_CH1, EXTERNAL_INT_3 },
  // { PORTA,  20, PIO_TIMER_ALT, PIN_ATTR_PWM_G, No_ADC_Channel, TCC0_CH0, NOT_ON_TIMER, EXTERNAL_INT_4 },
  // { PORTA, 21, PIO_DIGITAL, PIN_ATTR_PWM_G, No_ADC_Channel, TCC0_CH1, NOT_ON_TIMER, EXTERNAL_INT_5 },
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
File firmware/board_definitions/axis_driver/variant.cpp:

/*
  Copyright (c) 2014-2015 Arduino LLC.  All right reserved.

  This library is free software; you can redistribute it and/or
  modify it under the terms of the GNU Lesser General Public
  License as published by the Free Software Foundation; either
  version 2.1 of the License, or (at your option) any later version.

  This library is distributed in the hope that it will be useful,
  but WITHOUT ANY WARRANTY; without even the implied warranty of
  MERCHANTABILITY or FITNESS FOR A PARTICULAR PURPOSE.
  See the GNU Lesser General Public License for more details.

  You should have received a copy of the GNU Lesser General Public
  License along with this library; if not, write to the Free Software
  Foundation, Inc., 51 Franklin St, Fifth Floor, Boston, MA  02110-1301  USA
*/

#include "variant.h"

/*
 * Pins descriptions
 */

//TCC0 IOSET 6
//TCC1 IOSET 1
//TC0 IOSET 1
//TC1 IOSET 1
//TC2 IOSET 2
//TC3 IOSET 1
// //TC4 IOSET 1
//   EPortType       ulPort ;
//   uint32_t        ulPin ;
//   EPioType        ulPinType ;
//   uint32_t        ulPinAttribute ;
//   EAnalogChannel  ulADCChannelNumber ; /* ADC Channel number in the SAM device */
//   EPWMChannel     ulPWMChannel ;
//   ETCChannel      ulTCChannel ;
//   EExt_Interrupts ulExtInt ;


const PinDescription g_APinDescription[]=
{
//Auxiliary Ports
/* 0: AUX3 */       { PORTA,  2, PIO_DIGITAL, PIN_ATTR_DIGITAL, No_ADC_Channel, NOT_ON_PWM, NOT_ON_TIMER, EXTERNAL_INT_NONE },
/* 1: AUX4 */       { PORTA,  3, PIO_EXTINT, PIN_ATTR_DIGITAL, No_ADC_Channel, NOT_ON_PWM, NOT_ON_TIMER, EXTERNAL_INT_3 },
/* 2: AUX5 */       { PORTB,  4, PIO_DIGITAL, PIN_ATTR_DIGITAL, No_ADC_Channel, NOT_ON_PWM, NOT_ON_TIMER, EXTERNAL_INT_NONE },
/* 3: AUX6 */       { PORTB,  7, PIO_DIGITAL, PIN_ATTR_DIGITAL, No_ADC_Channel, NOT_ON_PWM, NOT_ON_TIMER, EXTERNAL_INT_NONE },
/* 4: AUX1 */       { PORTB,  30, PIO_DIGITAL, PIN_ATTR_DIGITAL, No_ADC_Channel, NOT_ON_PWM, NOT_ON_TIMER, EXTERNAL_INT_NONE },
/* 5: AUX2 */       { PORTB,  31, PIO_DIGITAL, PIN_ATTR_DIGITAL, No_ADC_Channel, NOT_ON_PWM, NOT_ON_TIMER, EXTERNAL_INT_NONE },

/* 6: NEOPIX */     { PORTB,  5, PIO_DIGITAL, PIN_ATTR_NONE, No_ADC_Channel, NOT_ON_PWM, NOT_ON_TIMER, EXTERNAL_INT_NONE },
/* 7: STAT_LED */   { PORTB,  13, PIO_DIGITAL, PIN_ATTR_DIGITAL, No_ADC_Channel, NOT_ON_PWM, NOT_ON_TIMER, EXTERNAL_INT_NONE },

/* 8: EN */         { PORTB, 12, PIO_DIGITAL, PIN_ATTR_NONE, No_ADC_Channel, NOT_ON_PWM, NOT_ON_TIMER, EXTERNAL_INT_NONE },
/* 9: DIR */        { PORTB,  8, PIO_DIGITAL, PIN_ATTR_DIGITAL, No_ADC_Channel, NOT_ON_PWM, NOT_ON_TIMER, EXTERNAL_INT_NONE },
/* 10: STEP */      { PORTB,  9, PIO_DIGITAL, PIN_ATTR_DIGITAL, No_ADC_Channel, NOT_ON_PWM, NOT_ON_TIMER, EXTERNAL_INT_NONE },
/* 11: MOTOR_M1 */  { PORTA,  10, PIO_OUTPUT, PIN_ATTR_NONE, No_ADC_Channel, NOT_ON_PWM, NOT_ON_TIMER, EXTERNAL_INT_NONE },
/* 12: M0 */        { PORTA,  11, PIO_OUTPUT, PIN_ATTR_NONE, No_ADC_Channel, NOT_ON_PWM, NOT_ON_TIMER, EXTERNAL_INT_NONE },
/* 13: INDEX */     { PORTA,  8, PIO_DIGITAL, PIN_ATTR_DIGITAL, No_ADC_Channel, NOT_ON_PWM, NOT_ON_TIMER, EXTERNAL_INT_NONE },
/* 14: DIAG */      { PORTA,  9, PIO_DIGITAL, PIN_ATTR_DIGITAL, No_ADC_Channel, NOT_ON_PWM, NOT_ON_TIMER, EXTERNAL_INT_NONE },
/* 15: SPREAD */    { PORTB,  11, PIO_DIGITAL, PIN_ATTR_DIGITAL, No_ADC_Channel, NOT_ON_PWM, NOT_ON_TIMER, EXTERNAL_INT_NONE },
/* 16: UART_TX */   { PORTA,  4, PIO_SERCOM_ALT, PIN_ATTR_DIGITAL, No_ADC_Channel, NOT_ON_PWM, NOT_ON_TIMER, EXTERNAL_INT_NONE },
/* 17: UART_RX */   { PORTA,  7, PIO_SERCOM_ALT, PIN_ATTR_DIGITAL, No_ADC_Channel, NOT_ON_PWM, NOT_ON_TIMER, EXTERNAL_INT_NONE },

/* 18: SDA2 */      { PORTA,  12, PIO_SERCOM, PIN_ATTR_DIGITAL, No_ADC_Channel, NOT_ON_PWM, NOT_ON_TIMER, EXTERNAL_INT_NONE },
/* 19: SCL2 */      { PORTA,  13, PIO_SERCOM, PIN_ATTR_DIGITAL, No_ADC_Channel, NOT_ON_PWM, NOT_ON_TIMER, EXTERNAL_INT_NONE },
/* 20: SDA1 */      { PORTA,  22, PIO_SERCOM, PIN_ATTR_DIGITAL, No_ADC_Channel, NOT_ON_PWM, NOT_ON_TIMER, EXTERNAL_INT_NONE },
/* 21: SCL1 */      { PORTA,  23, PIO_SERCOM, PIN_ATTR_DIGITAL, No_ADC_Channel, NOT_ON_PWM, NOT_ON_TIMER, EXTERNAL_INT_NONE },
/* 22: SYNC */      { PORTA,  14, PIO_DIGITAL, PIN_ATTR_DIGITAL, No_ADC_Channel, NOT_ON_PWM, NOT_ON_TIMER, EXTERNAL_INT_NONE }, 

/* 23: EEPROM_CS */ { PORTA,  21, PIO_DIGITAL, PIN_ATTR_DIGITAL, No_ADC_Channel, NOT_ON_PWM, NOT_ON_TIMER, EXTERNAL_INT_NONE },
/* 24: ETH_CS */    { PORTB,  1, PIO_DIGITAL, PIN_ATTR_DIGITAL, No_ADC_Channel, NOT_ON_PWM, NOT_ON_TIMER, EXTERNAL_INT_NONE },
/* 25: MOSI */      { PORTB,  2, PIO_SERCOM_ALT, PIN_ATTR_DIGITAL, No_ADC_Channel, NOT_ON_PWM, NOT_ON_TIMER, EXTERNAL_INT_NONE  },
/* 26: MISO */      { PORTB,  0, PIO_SERCOM_ALT, PIN_ATTR_DIGITAL, No_ADC_Channel, NOT_ON_PWM, NOT_ON_TIMER, EXTERNAL_INT_NONE },
/* 27: SCK */       { PORTB,  3, PIO_SERCOM_ALT, PIN_ATTR_DIGITAL, No_ADC_Channel, NOT_ON_PWM, NOT_ON_TIMER, EXTERNAL_INT_NONE },

/* 28: USB_V*/      { PORTA,  6, PIO_ANALOG, (PIN_ATTR_ANALOG|PIN_ATTR_PWM_E), ADC_Channel6, TC1_CH0, TC1_CH0, EXTERNAL_INT_6 },
/* 29: BUS_V*/      { PORTB,  6, PIO_ANALOG, PIN_ATTR_ANALOG_ALT, ADC_Channel8, NOT_ON_PWM, NOT_ON_TIMER, EXTERNAL_INT_6 },

/* 30: USR_INPUT */   { PORTA,  15, PIO_INPUT_PULLUP, PIN_ATTR_DIGITAL, No_ADC_Channel, NOT_ON_PWM, NOT_ON_TIMER, EXTERNAL_INT_NONE }


};

const void* g_apTCInstances[TCC_INST_NUM+TC_INST_NUM]={ TCC0, TCC1, TCC2, TCC3, TCC4, TC0, TC1, TC2, TC3, TC4, TC5 } ;
const uint32_t GCLK_CLKCTRL_IDs[TCC_INST_NUM+TC_INST_NUM] = { TCC0_GCLK_ID, TCC1_GCLK_ID, TCC2_GCLK_ID, TCC3_GCLK_ID, TCC4_GCLK_ID, TC0_GCLK_ID, TC1_GCLK_ID, TC2_GCLK_ID, TC3_GCLK_ID, TC4_GCLK_ID, TC5_GCLK_ID } ;

// Multi-serial objects instantiation
SERCOM sercom0( SERCOM0 ) ;
SERCOM sercom1( SERCOM1 ) ;
SERCOM sercom2( SERCOM2 ) ;
SERCOM sercom3( SERCOM3 ) ;
SERCOM sercom4( SERCOM4 ) ;
SERCOM sercom5( SERCOM5 ) ;

Uart Serial1( &sercom0, PIN_SERIAL1_RX, PIN_SERIAL1_TX, PAD_SERIAL1_RX, PAD_SERIAL1_TX ) ;

void SERCOM0_0_Handler()
{
  Serial1.IrqHandler();
}
void SERCOM0_1_Handler()
{
  Serial1.IrqHandler();
}
void SERCOM0_2_Handler()
{
  Serial1.IrqHandler();
}
void SERCOM0_3_Handler()
{
  Serial1.IrqHandler();
}

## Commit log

2023-11-18 working simple communication with TMC2209
2023-11-18 motor moves, low torque
2023-11-19 dont even know
2023-11-19 somewhat runs
2023-11-21 update to custom library
2023-11-22 update to new library
2023-11-22 add limit search
2023-12-01 compontents placed
2024-02-20 compete samd21 board
2024-02-25 PCB layout and routing complete
2024-02-25 move file and add HAT
2024-03-01 board tweaks and outputs for jlcpcb
2024-06-12 New rev for base board
2024-06-19 PCB ordered
2024-06-22 Add 32Mhz crystal
2024-06-23 PCB V2 draft
2024-06-26 PCB v2 ordered
2024-06-27 Start message defines
2024-07-01 Create interfaces between modules
2024-07-02 Create serial interface tester
2024-07-30 Update for PCB V2 pins
2024-07-30 missed connections
2024-08-01 Move pins for addressable LED
2024-08-01 track uf2 bootloader
2024-08-03 cherry pick led driver from branch
2024-08-03 Fix pin mapping to enable addressable led
2024-08-03 Implement neopixel rainbow
2024-08-04 Copy variant and board defenition for custom pin mappings
2024-08-04 change variant to use axis_basic variant
2024-08-04 customize ardiuno pins and create additional neopixel states
2024-08-10 Working encoder and position filtering
2024-08-11 Update SERCOM pins
2024-08-13 'whip'
2024-08-18 Absoute motor positioning from encoder
2024-08-18 Move FastLed library to keep config from changing
2024-08-22 change name to driver
2024-08-23 PCB V1.0.0 Ordered
2024-08-25 Fix missed connections
2024-08-26 Consistent motor control setup
2024-09-01 Power error and update for V1.0.0 PCB
2024-09-01 Set LED state implemented
2024-09-07 Correct motor phase naming
2024-09-22 test movement program
2024-10-10 Refine tmc initialization
2024-10-11 Json over serial works
2024-10-11 start message set
2024-10-11 Start on high level architecture
2024-10-13 LED and motor examples
2024-10-14 Encoder interface updates
2024-10-19 PCB V1.1.0
2024-10-23 Fix resistor values
2024-10-25 Add Get Velocity command
2024-11-17 EthernetHat ordered
2024-11-25 Add ethernet libraries, working mac read from eeprom
2024-11-26 read serial number from flash
2024-11-26 Complete test for flash
2024-11-28 EthernetHat V1.2.0 ordered
2024-12-11 Ethernet HAT V1.2.0
2024-12-24 Detect ethnet hat
2025-01-01 Add option to print flash buffer
2025-01-01 revert to before ethernet changes
2025-01-01 Control of led over byte message
2025-01-01 Byte message controlling LED
2025-01-01 Make python messages simpler
2025-01-01 Include C example
2025-01-03 Start new message descriptions
2025-01-03 Finish led messages
2025-01-03 Add description, remove json requirement
2025-01-03 Include settings messages
2025-01-04 Remove message handlers from device code, finish led interface
2025-01-10 Move to single message handler, correct serial interface
2025-01-10 LED test complete
2025-01-10 auto python message generator, motr control
2025-01-11 CHange motor names
2025-01-11 Update flash part number
2025-01-11 relative position setting
2025-01-13 Include all enums
2025-01-14 Add max speed and acceleration to message set
2025-01-26 Refactor Led Controller to use a queue
2025-02-05 Home Direction
2025-02-05 Remove Prints
2025-02-23 Scara example
2025-02-24 led control with pwm
2025-02-24 simple pwm working with timer
2025-02-24 more taken out
2025-02-25 hardware timer
2025-02-28 simple flashing
2025-03-01 simple gpio timer
2025-03-01 steps working
2025-03-04 simple timer functionality
2025-03-04 initial timer stuff
2025-03-04 inturupt driven run
2025-03-04 run distance
2025-03-05 working test
2025-03-05 initial working demo
2025-03-05 change step count
2025-03-05 Corrected step high time
2025-03-05 needed more delay
2025-03-09 Add step and velocity mode
2025-03-10 Working basic interpolation
2025-03-10 Scara line
2025-03-12 Working Ethernet Comms
2025-03-13 Ethernet fix
2025-03-14 Correct velocity step not starting steps correctly
2025-03-15 initial
2025-03-16 Initial implementation
2025-03-18 python class generation complete
2025-03-18 Python Getters and Setters
2025-03-18 Add Id to messages
2025-03-18 Add Enums
2025-03-19 begin cpp implementation
2025-03-28 missed f
2025-03-28 remove spline
2025-03-30 Add Set Home Speed Message
2025-03-30 Make timer period change for each step
2025-03-30 Missed functions
2025-03-31 Sensorless Homing
2025-03-31 Home State
2025-04-02 Issues with sensorless homing, revert to encoder homing
2025-05-24 Refactor home direction handling and update message types for consistency
2025-05-24 Move Ethernet code
2025-05-26 MQTT functionality
2025-05-26 initial web server
2025-05-26 mqtt velocity and position control
2025-05-30 Sync bytes
2025-05-31 Python Settings
2025-05-31 slow read
2025-06-01 Refactor message buffer handling and update UI for Home Assistant settings
2025-06-02 initial flatbuffers
2025-06-04 Fails to compile
2025-07-20 get version message simple flatbuffer implementation
2025-10-17 shift to readme defined protocol
2025-10-17 Send ACK for SetI2C/SetEthernet, relocate LED handlers, expand protocol tests, and reorder GetVersion doc
    - MessageProcessor.cpp
    - Ensure ACK responses are sent for SetI2CAddress and SetEthernetAddress commands.
    - Move SetLedColor/GetLedColor cases to a later position in the switch for clearer grouping.
    - Minor comment spacing cleanup.
    - examples/Python/ProtocolTest.py
    - Expand protocol test: add Set/Get I2C and Set/Get Ethernet tests with ACK handling and additional debug output.
2025-10-17 reorder cases
2025-10-17 add all tests
2025-10-26 Update protocol IDs and LED sequencing; add parsing, robust tests, and ACK handling
2025-11-14 Add message checksums, fix LED handling, and create web configurator frontend
2025-11-14 Gimbal
2025-11-26 Refactor DualMotorGimbal to simplified position controller, remove GUI/velocity code; add GimbalGearingTest; add debug log to SetVelocityAndStepsMessage
2025-11-26 Add connection indicator UI and improve serial connection status handling
    - Wrap "Connect" button in a .connection-controls container and add a .connection-indicator element in index.html
    - Initialize and toggle the indicator element in script.js (set classes on DOMContentLoaded, connecting, connected, disconnected)
    - Add Web Serial API support check with user alert and clearer status messages on failure
    - Log connect button clicks for easier debugging
    - Update readLoop error handling to mark connection lost and update indicator/status
    - Add styling, animations and state styles for .connection-controls and .connection-indicator in style.css
2025-11-26 Remove legacy Messages.h; simplify LED controller and add activity indicators
    - Delete firmware/include/Messages.h (old message/type definitions removed)
    - Simplify AddrLedController::OnRun to use executionPeriod and immediately show queued steps (remove internal millis timing)
    - Minor formatting cleanup for AddLedStep
    - Add LED activity cues:
    - flash green briefly on incoming byte messages (MessageProcessor::HandleByteMsg)
    - flash blue briefly when sending messages (MessageProcessor::SendMsg)
2025-12-01 Add web configurator frontend and improve serial/UI handling; tweak LED activity
    - Add web_configurator frontend (index.html, style.css, README) with retro "AXIS CONTROL TERMINAL" UI, terminal effects, connection indicator, timestamp, and reorganized controls.
    - Add local server launcher and server script (start_server.sh, serve.py) to serve configurator over HTTP.
    - Enhance script.js: start/boot effects, timestamp updates, richer connection state text, robust serial buffer parsing with resync, checksum verification, extensive TX/RX logging, safer message handl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
    - Fix IP byte order handling (ipToString/stringToIp) to match little-endian wire fo
2025-12-01 Add disconnect and "poll all settings" to web configurator; implement serial disconnect and pollAllSettings; shorten LED activity pulses on RX/TX
2025-12-03 Replace direct Serial output with DEBUG_PRINT macros in EncoderController and MotorController
2025-12-03 Add UDP position test and UDP transport support for web configurator
    - Add examples/Python/UDPPositionControlTest.py: new comprehensive UDP-based
    position control test using AxisUDP/AxisProtocol (connection, retries,
    position/relative/absolute tests, LED feedback, save config, interactive run).
    - web_configurator/index.html: add connection type selector (Serial/UDP) and
    shortcut UDP target IP/port inputs.
    - web_configurator/script.js: support UDP mode:
2025-12-03 Migrate web configurator server from SimpleHTTPRequestHandler to Flask backend
    - Replace custom ThreadingHTTPServer + CustomHTTPRequestHandler with a Flask app
    - Serve static UI files via Flask and add routes:
    - POST /udp/send to send base64 payloads over UDP (with validation and JSON responses)
    - GET /udp/stream as an SSE endpoint for incoming UDP packets
    - Switch SSE client model to per-client queue objects; udp_receiver_loop pushes JSON/base64 payloads to queues
    - Lazily create and bind shared UDP socket and start receiver thread on first send
